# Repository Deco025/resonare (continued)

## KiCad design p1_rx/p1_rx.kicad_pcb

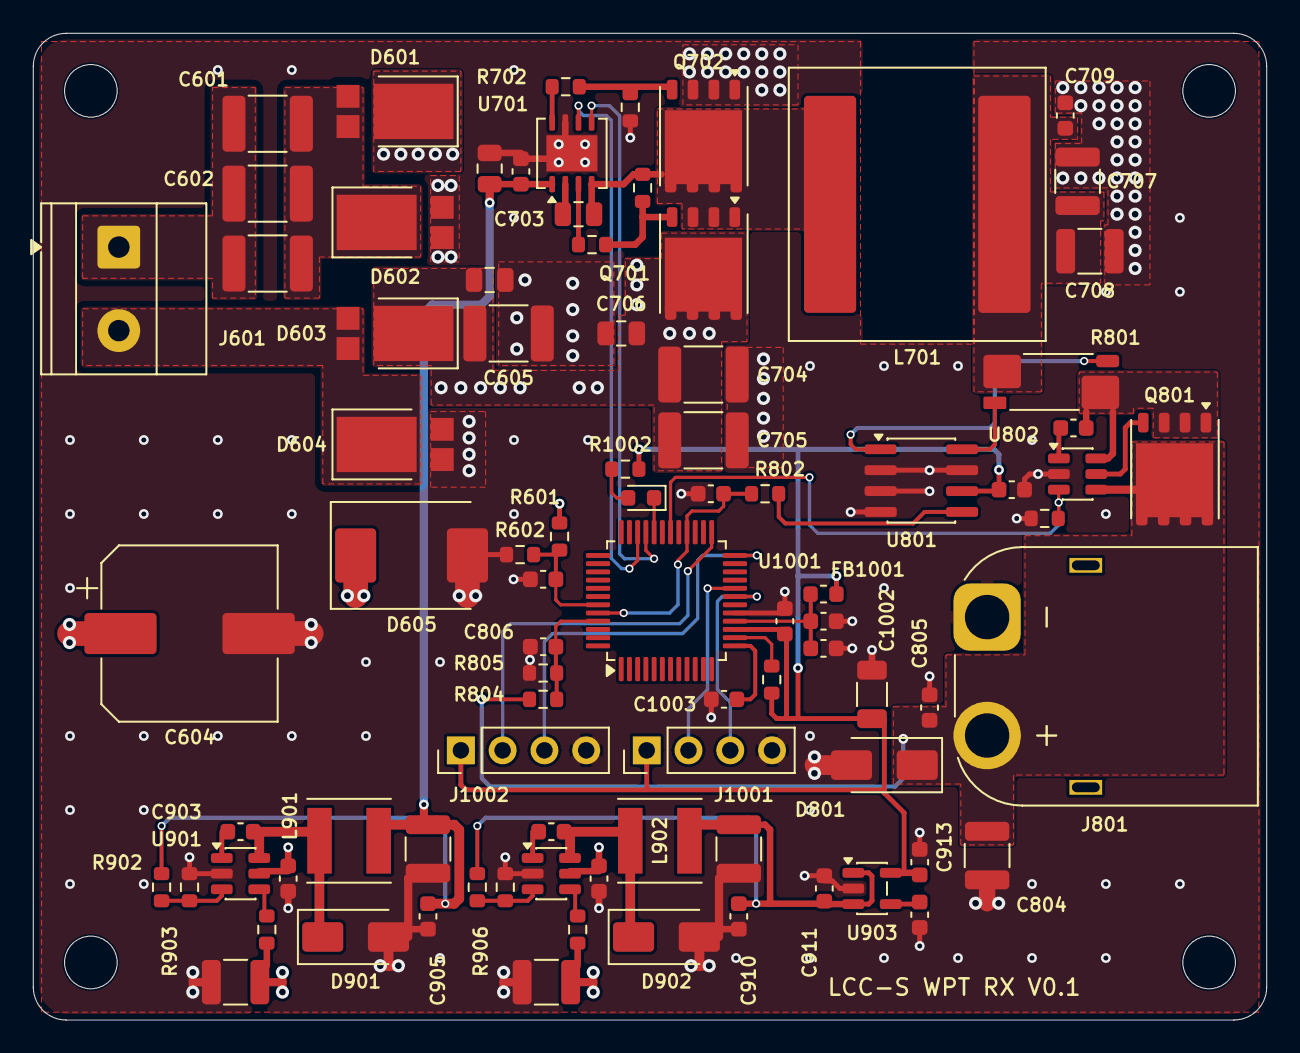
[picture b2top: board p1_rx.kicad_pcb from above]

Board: 4 copper layers, 75.0 x 60.0 mm, 90 parts (0 on the bottom side), 46 nets.

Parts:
C601: 56nF; C_1812_4532Metric
C602: 4.7nF; C_1812_4532Metric
C603: 470pF; C_1812_4532Metric
C604: 100uF; CP_Elec_10x10.5
C605, C704, C705: 10uF; C_1812_4532Metric
C606, C706: 100nF; C_0805_2012Metric
C607, C702, C709, C801, C803, C805, C806, C902, C903, C905, C907, C908, C910, C1001, C1003, C1005: 100nF; C_0603_1608Metric
C701: 2.2uF; C_0805_2012Metric
C703: 220nF; C_0805_2012Metric
C707, C708, C804, C904, C909: 22uF; C_1210_3225Metric
C802: 1nF; C_0603_1608Metric
C901, C906: 4.7uF; C_1210_3225Metric
C911, C913, C1004: 1uF; C_0603_1608Metric
C912: 10nF; C_0603_1608Metric
C1002: 22uF; C_1206_3216Metric
D601, D602, D603, D604: SB2060L; D_PowerDI-5
D605: SMCJ33A; D_SMC
D801: SMAJ26A; D_SMA
D901, D902: SS110; D_SMA
D1001: LED_G; LED_0603_1608Metric
FB1001: 600R@100MHz; L_0603_1608Metric
H1, H2, H3, H4: M3; MountingHole_3.2mm_M3
J601: RX_COIL; TerminalBlock_Phoenix_MKDS-1,5-2-5.08_1x02_P5.08mm_Horizont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
J801: XT60_SUPERCAP; AMASS_XT60PW-M_1x02_P7.20mm_Horizontal
J1001: ISP; PinHeader_1x04_P2.54mm_Vertical
J1002: UART_LINK; PinHeader_1x04_P2.54mm_Vertical
L701: 15uH; L_Coilcraft_XAL1510-153
L901: 56uH; L_Taiyo-Yuden_NR-50xx
L902: 33uH; L_Taiyo-Yuden_NR-50xx
Q701, Q702, Q801: BSC070N10NS3G; Infineon_PG-TDSON-8_6.15x5.15mm
R601, R804: 150k; R_0603_1608Metric
R602, R703, R704, R805, R903, R906, R1001: 10k; R_0603_1608Metric
R701, R702: 10R; R_0603_1608Metric
R801: 2m; R_Shunt_Vishay_WSK2512_6332Metric_T1.19mm
R802: 100; R_0603_1608Metric
R803, R901, R904: 100k; R_0603_1608Metric
R902: 147k; R_0603_1608Metric
R905: 54.9k; R_0603_1608Metric
R1002: 1k; R_0603_1608Metric
U701: UCC27211; HVSON-8-1EP_4x4mm_P0.8mm_EP2.2x3.1mm
U801: INA240A2D; SOIC-8_3.9x4.9mm_P1.27mm
U802: LM74700; SOT-23-6
U901, U902: LMR16006X; SOT-23-6
U903: TC2185-3.3; SOT-23-5
U1001: STC32G12K128; LQFP-48_7x7mm_P0.5mm

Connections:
+3V3_RX: C801.1, C913.1, C1001.1, C1002.1, FB1001.1, J1001.1, J1002.1, R1001.1, R1002.1, U801.6, U903.5, U1001.15
+5V_RX: C909.1, C910.1, C911.1, L902.2, R905.1, U903.1, U903.3
+12V_RX: C701.1, C702.1, C904.1, C905.1, L901.2, R902.1, U701.1
/RX_AuxPower/FB_5V_RX: R905.2, R906.1, U902.3
/RX_AuxPower/FB_12V_RX: R902.2, R903.1, U901.3
/RX_AuxPower/SW_5V_RX: C908.2, D902.1, L902.1, U902.6
/RX_AuxPower/SW_12V_RX: C903.2, D901.1, L901.1, U901.6
/RX_Buck/BUCK_SW: C703.2, L701.1, Q701.1, Q701.2, Q701.3, Q702.5, R703.2, U701.4
/RX_CoilRect/RX_AC1: C601.2, C602.2, C603.2, D601.2, D602.1
/RX_CoilRect/RX_AC2: D603.2, D604.1, J601.2
/RX_CoilRect/RX_COIL1: C601.1, C602.1, C603.1, J601.1
/RX_MCU/ISP_RXD: J1001.3, U1001.19
/RX_MCU/ISP_TXD: J1001.2, U1001.20
/RX_MCU/LINK_RX: J1002.3, U1001.24
/RX_MCU/LINK_TX: J1002.2, U1001.25
/RX_MCU/VREF_RX: C1004.1, C1005.1, FB1001.2, U1001.16
/RX_Output/CHG_OUT: C803.2, Q801.1, Q801.2, Q801.3, R801.4, U802.6
/RX_Output/ISNS_CHG_N: R801.3, U801.1
/RX_Output/ISNS_CHG_P: R801.2, U801.8
BUCK_OUT: C707.1, C708.1, C709.1, L701.2, R801.1
CHG_EN: R803.1, U802.3, U1001.30
GND_RX: C604.2, C605.2, C606.2, C607.2, C701.2, C702.2, C704.2, C705.2, C706.2, C707.2, C708.2, C709.2, C801.2, C802.2, C804.2, C805.2, C806.2, C901.2, C902.2, C904.2, C905.2, C906.2, C907.2, C909.2, C910.2, C911.2, C912.2, C913.2, C1001.2, C1002.2, C1003.1, C1004.2, C1005.2, D602.2, D604.2, D605.2, D801.2, D901.2, D902.2, J801.1, J1001.4, J1002.4, Q702.1, Q702.2, Q702.3, R602.2, R704.2, R803.2, R805.2, R903.2, R906.2, U701.7, U701.9, U801.2, U801.3, U801.4, U801.7, U802.2, U901.2, U902.2, U903.2, U1001.17
ISNS_CHG: C802.1, R802.2, U1001.28, U1001.44
unnamed: D1001.2, R1002.2
unnamed: D1001.1, U1001.32
unnamed: Q701.4, R701.2, R703.1
unnamed: Q702.4, R702.2, R704.1
unnamed: Q801.4, U802.5
unnamed: R802.1, U801.5
unnamed: C703.1, U701.2
unnamed: R701.1, U701.3
unnamed: R702.1, U701.8
unnamed: C803.1, U802.1
unnamed: C903.1, U901.1
unnamed: R901.2, U901.4
unnamed: C908.1, U902.1
unnamed: R904.2, U902.4
unnamed: C912.1, U903.4
unnamed: R1001.2, U1001.14
unnamed: C1003.2, U1001.13
PWM_BUCK_H: U701.5, U1001.33
PWM_BUCK_L: U701.6, U1001.34
VRECT: C604.1, C605.1, C606.1, C704.1, C705.1, C706.1, C901.1, C902.1, C906.1, C907.1, D601.1, D603.1, D605.1, Q701.5, R601.1, R901.1, R904.1, U901.5, U902.5
VRECT_SNS: C607.1, R601.2, R602.1, U1001.43
VSCAP: C804.1, C805.1, D801.1, J801.2, Q801.5, R804.1, U802.4
VSCAP_SNS: C806.1, R804.2, R805.1, U1001.45

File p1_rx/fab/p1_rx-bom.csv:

"Refs","Value","Voltage","Footprint","Qty","DNP"
"C601","56nF","250V C0G","Capacitor_SMD:C_1812_4532Metric","1",""
"C602","4.7nF","250V C0G","Capacitor_SMD:C_1812_4532Metric","1",""
"C603","470pF","250V C0G","Capacitor_SMD:C_1812_4532Metric","1",""
"C604","100uF","63V","Capacitor_SMD:CP_Elec_10x10.5","1",""
"C605,C704,C705","10uF","63V","Capacitor_SMD:C_1812_4532Metric","3",""
"C606,C706","100nF","100V","Capacitor_SMD:C_0805_2012Metric","2",""
"C607,C702,C709,C801,C803,C805,C806,C903,C905,C908,C910,C1001,C1003,C1005","100nF","","Capacitor_SMD:C_0603_1608Metric","14",""
"C701","2.2uF","25V","Capacitor_SMD:C_0805_2012Metric","1",""
"C703","220nF","50V","Capacitor_SMD:C_0805_2012Metric","1",""
"C707,C708","22uF","35V","Capacitor_SMD:C_1210_3225Metric","2",""
"C802","1nF","","Capacitor_SMD:C_0603_1608Metric","1",""
"C804","22uF","","Capacitor_SMD:C_1210_3225Metric","1",""
"C901,C906","4.7uF","100V","Capacitor_SMD:C_1210_3225Metric","2",""
"C902,C907","100nF","100V","Capacitor_SMD:C_0603_1608Metric","2",""
"C904","22uF","25V","Capacitor_SMD:C_1210_3225Metric","1",""
"C909","22uF","16V","Capacitor_SMD:C_1210_3225Metric","1",""
"C911,C913,C1004","1uF","","Capacitor_SMD:C_0603_1608Metric","3",""
"C912","10nF","","Capacitor_SMD:C_0603_1608Metric","1",""
"C1002","22uF","16V","Capacitor_SMD:C_1206_3216Metric","1",""
"D601,D602,D603,D604","SB2060L","","Diode_SMD:D_PowerDI-5","4",""
"D605","SMCJ33A","","Diode_SMD:D_SMC","1",""
"D801","SMAJ26A","","Diode_SMD:D_SMA","1",""
"D901,D902","SS110","","Diode_SMD:D_SMA","2",""
"D1001","LED_G","","LED_SMD:LED_0603_1608Metric","1",""
"FB1001","600R@100MHz","","Inductor_SMD:L_0603_1608Metric","1",""
"J601","RX_COIL","","TerminalBlock_Phoenix:TerminalBlock_Phoenix_MKDS-1,5-2-5.08_1x02_P5.08mm_Horizontal","1",""
"J801","XT60_SUPERCAP","","Connector_AMASS:AMASS_XT60PW-M_1x02_P7.20mm_Horizontal","1",""
"J1001","ISP","","Connector_PinHeader_2.54mm:PinHeader_1x04_P2.54mm_Vertical","1",""
"J1002","UART_LINK","","Connector_PinHeader_2.54mm:PinHeader_1x04_P2.54mm_Vertical","1",""
"L601","20uH","","","1",""
"L701","15uH","","Inductor_SMD:L_Coilcraft_XAL1510-153","1",""
"L901","56uH","","Inductor_SMD:L_Taiyo-Yuden_NR-50xx","1",""
"L902","33uH","","Inductor_SMD:L_Taiyo-Yuden_NR-50xx","1",""
"Q701,Q702,Q801","BSC070N10NS3G","","Package_SON:Infineon_PG-TDSON-8_6.15x5.15mm","3",""
"R601,R804","150k","","Resistor_SMD:R_0603_1608Metric","2",""
"R602,R703,R704,R805,R903,R906,R1001","10k","","Resistor_SMD:R_0603_1608Metric","7",""
"R701,R702","10R","","Resistor_SMD:R_0603_1608Metric","2",""
"R801","2m","","Resistor_SMD:R_Shunt_Vishay_WSK2512_6332Metric_T1.19mm","1",""
"R802","100","","Resistor_SMD:R_0603_1608Metric","1",""
"R803,R901,R904","100k","","Resistor_SMD:R_0603_1608Metric","3",""
"R902","147k","","Resistor_SMD:R_0603_1608Metric","1",""
"R905","54.9k","","Resistor_SMD:R_0603_1608Metric","1",""
"R1002","1k","","Resistor_SMD:R_0603_1608Metric","1",""
"U701","UCC27211","","Package_SON:HVSON-8-1EP_4x4mm_P0.8mm_EP2.2x3.1mm","1",""
"U801","INA240A2D","","Package_SO:SOIC-8_3.9x4.9mm_P1.27mm","1",""
"U802","LM74700","","Package_TO_SOT_SMD:SOT-23-6","1",""
"U901,U902","LMR16006X","","Package_TO_SOT_SMD:SOT-23-6","2",""
"U903","TC2185-3.3","","Package_TO_SOT_SMD:SOT-23-5","1",""
"U1001","STC32G12K128","","Package_QFP:LQFP-48_7x7mm_P0.5mm","1",""
